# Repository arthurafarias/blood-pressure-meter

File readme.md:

# IoT Measurement Endpoint

A KiCad PCB design for a wireless IoT node that reads analog sensors and drives actuators (DC motor and solenoid valve). Built around the ESP32-C3 module for WiFi/BLE connectivity.

## Features

- **ESP32-C3-WROOM-02** — WiFi 4 + Bluetooth LE microcontroller module
- **Analog sensor front-end** — LM324 quad op-amp for signal conditioning
- **Actuator outputs** — DMC2053UVT complementary MOSFET pair for a DC motor and a solenoid valve
- **USB-C** — CH330N USB-to-UART bridge for programming and serial debug; TVS + common-mode choke for ESD/EMI protection
- **Power** — battery connector with 5V USB-C input; NCP1117-3.3 LDO generates the 3.3V rail; polyfuse (0402L050SL) for overcurrent protection
- **User interface** — tactile push buttons (KMR232NG) and status LEDs
- **Fabrication aids** — fiducials, mounting holes, and test points throughout

## Schematic sheets

| Sheet | Contents |
|---|---|
| Top-level | Sheet hierarchy and inter-sheet connections |
| Microcontroller | ESP32-C3-WROOM-02 and decoupling |
| Sensor | LM324 op-amp conditioning circuit |
| Motor | DC motor MOSFET driver with flyback diode |
| Valve | Solenoid valve MOSFET driver |
| 3.3V Regulator | NCP1117-3.3 LDO and bulk capacitors |
| USB Connector | USB-C, CH330N, common-mode choke, TVS array |
| Battery Connector | Battery input and protection diodes |
| Buttons | Tactile switch debounce network |
| LEDs | Status indicators |

## Power architecture

```
USB-C (5V) ──┬── CH330N (serial) ──► UART ──► ESP32-C3
             │
Battery ─────┴── NCP1117-3.3 ──► 3.3V rail ──► ESP32-C3, LM324, logic
                                               └── actuator gate drives

Actuators driven from +6V / +5V rail (motor, valve)
```

## Key components

| Reference | Part | Description |
|---|---|---|
| U (MCU) | ESP32-C3-WROOM-02 | WiFi 4 / BLE 5 module |
| U (USB) | CH330N | USB-to-UART converter, SOIC-8 |
| U (reg) | NCP1117-3.3 | 1A LDO, SOT-223 |
| U (amp) | LM324 | Quad op-amp, DIP-14/SOIC-14 |
| Q | DMC2053UVT | Complementary P+N MOSFET pair, TSOT-23-6 |
| D (ESD) | ESD9B5.0ST5G | TVS diode, signal lines |
| D (USB TVS) | WE-TVS-82400102 | Low-cap TVS array, SOT-23-6 |
| L (USB filter) | 0603USB-142 | Common-mode choke, 98nH, 500mA |
| F | 0402L050SL | Resettable polyfuse |
| SW | KMR232NG ULC LFS | Tactile push button |

## Tools

- **EDA**: KiCad 10.0
- **Simulation**: ngspice (`.cir` files in repo for op-amp circuit verification)
- **3D export**: STEP / STL / GLB (see `iot-measurement-endpoint.step`)

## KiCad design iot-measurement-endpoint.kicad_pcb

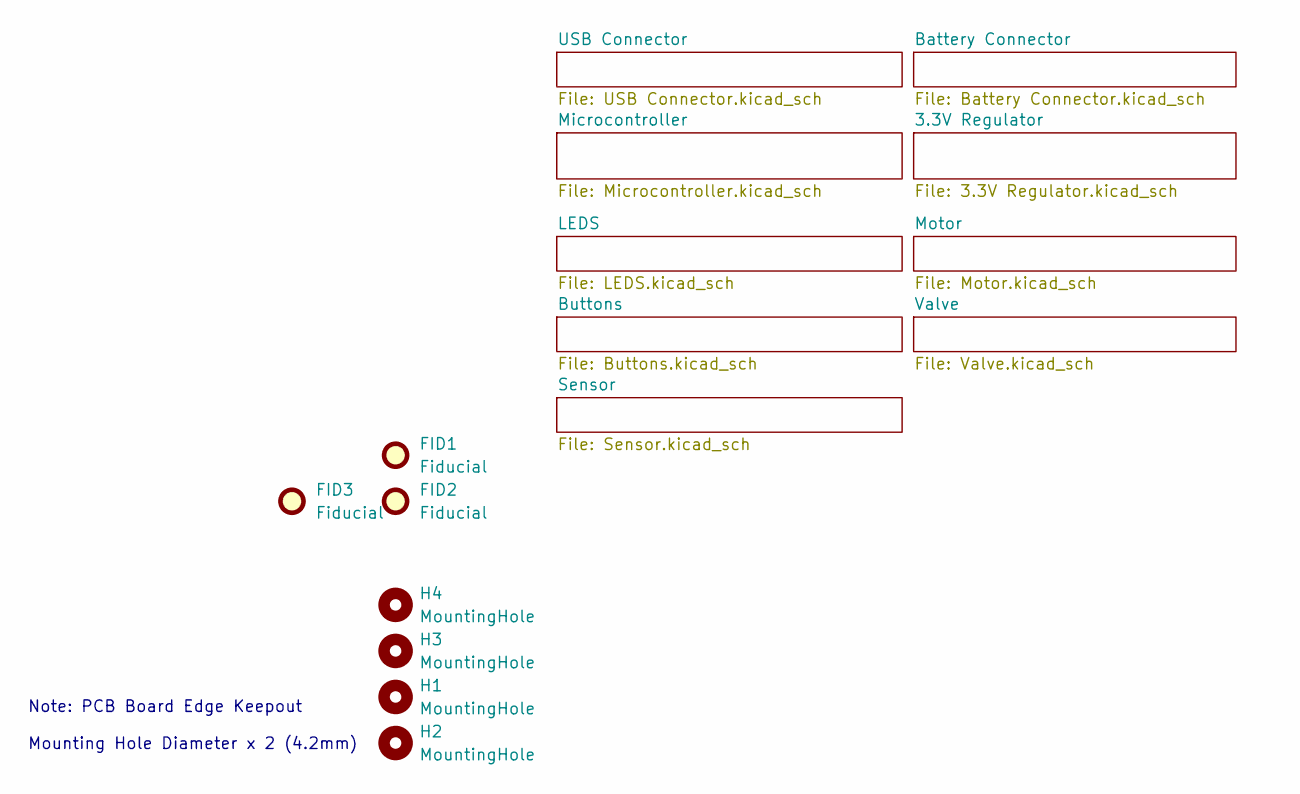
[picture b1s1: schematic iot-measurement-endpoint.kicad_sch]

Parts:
FID1: Fiducial; Fiducial_Cross_1.5mm_Mask2mm
FID2, FID3: Fiducial; Fiducial_0.5mm_Mask1.5mm
H1, H2, H3, H4: MountingHole; MountingHole_2.1mm

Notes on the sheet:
Note: PCB Board Edge Keepout Mounting Hole Diameter x 2 (4.2mm)

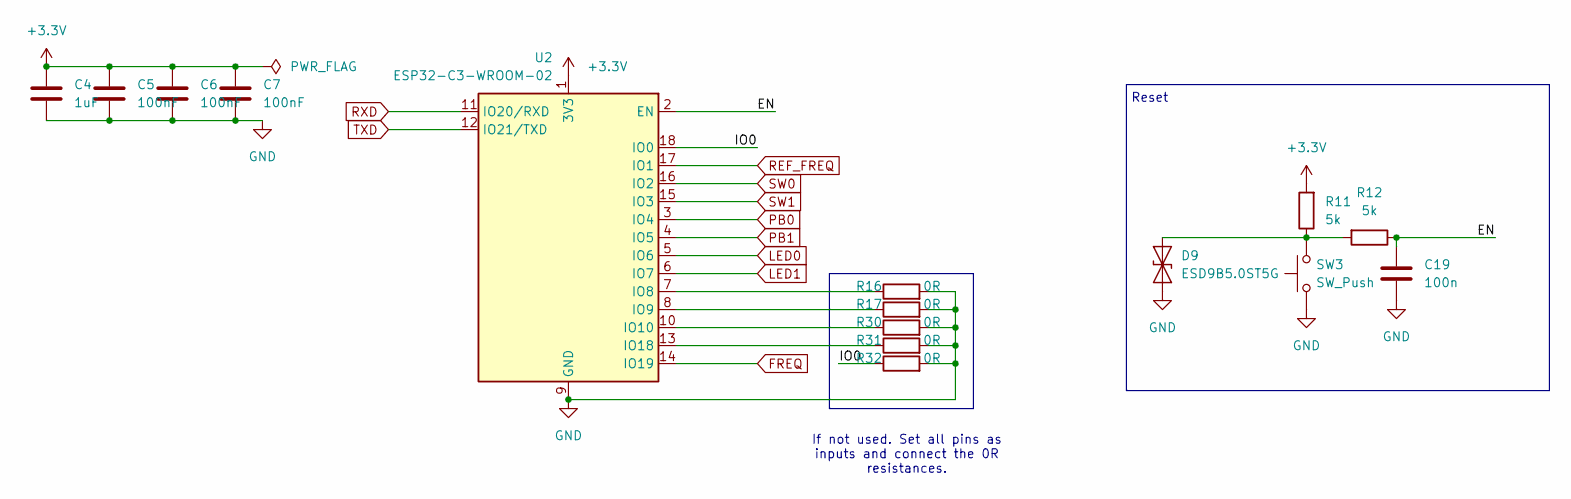
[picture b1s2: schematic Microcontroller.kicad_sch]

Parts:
C4: 1uF; C_0402_1005Metric
C5, C6, C7: 100nF; C_0402_1005Metric
C19: 100n; C_0402_1005Metric
D9: ESD9B5.0ST5G; D_SOD-923
R11, R12: 5k; R_0402_1005Metric
R16, R17, R30, R31, R32: 0R; R_0402_1005Metric
SW3: SW_Push; SW_Push_1P1T_NO_CK_KMR2
U2: ESP32-C3-WROOM-02

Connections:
+3.3V: C4.1, C5.1, C6.1, C7.1, R11.2, U2.1 (3V3); also elsewhere on the board
/Microcontroller/EN: C19.1, R12.1, U2.2 (EN)
/Microcontroller/IO0: R32.1, U2.18 (IO0)
FREQ: U2.14 (IO19); also elsewhere on the board
GND: C4.2, C5.2, C6.2, C7.2, C19.2, D9.1 (A1), R16.2, R17.2, R30.2, R31.2, R32.2, SW3.1, U2.9 (GND), U2.19 (GND); also elsewhere on the board
LED0: U2.5 (IO6); also elsewhere on the board
LED1: U2.6 (IO7); also elsewhere on the board
unnamed: D9.2 (A2), R11.1, R12.2, SW3.2
unnamed: R16.1, U2.7 (IO8)
unnamed: R17.1, U2.8 (IO9)
unnamed: R30.1, U2.10 (IO10)
unnamed: R31.1, U2.13 (IO18)
PB0: U2.3 (IO4); also elsewhere on the board
PB1: U2.4 (IO5); also elsewhere on the board
REF_FREQ: U2.17 (IO1); also elsewhere on the board
RXD: U2.11 (IO20/RXD); also elsewhere on the board
SW0: U2.16 (IO2); also elsewhere on the board
SW1: U2.15 (IO3); also elsewhere on the board
TXD: U2.12 (IO21/TXD); also elsewhere on the board

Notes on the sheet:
Reset
If not used. Set all pins as inputs and connect the 0R resistances.

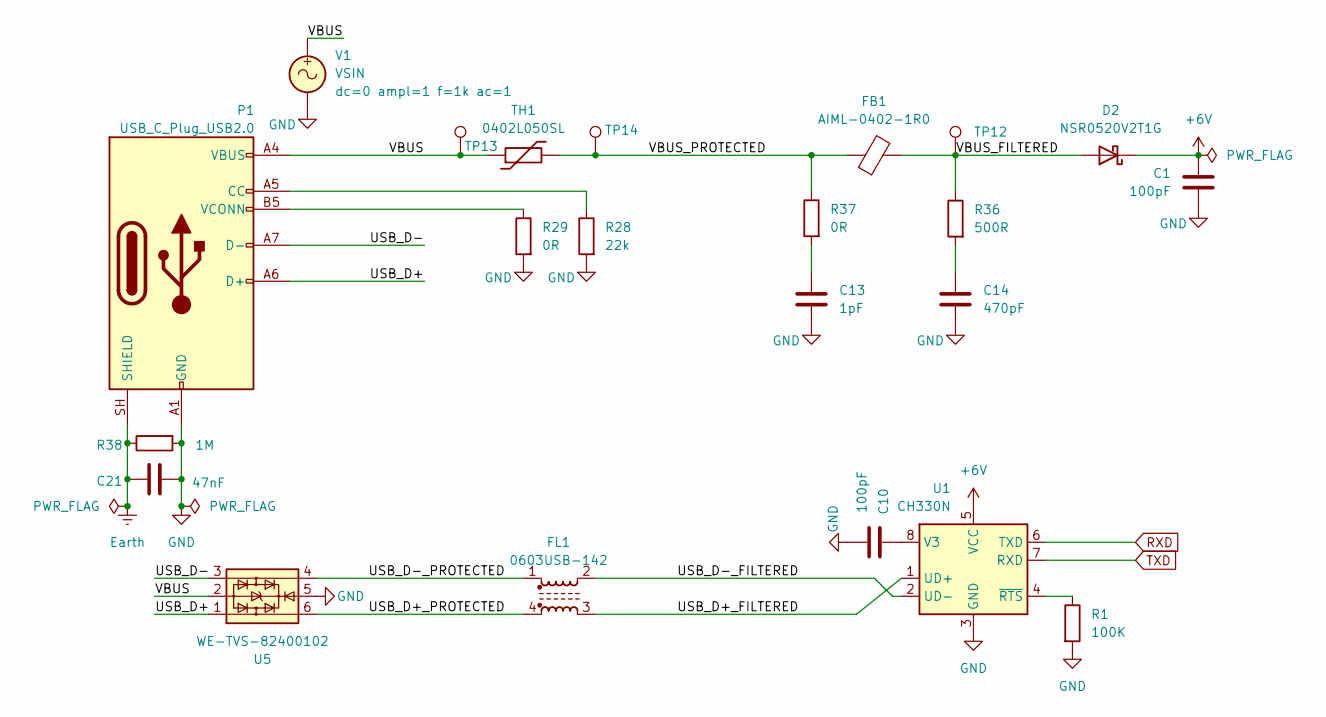
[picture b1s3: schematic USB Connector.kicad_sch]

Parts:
C1, C10: 100pF; C_0402_1005Metric
C13: 1pF; C_0402_1005Metric
C14: 470pF; C_0402_1005Metric
C21: 47nF; C_0402_1005Metric
D2: NSR0520V2T1G; D_0402_1005Metric
FB1: AIML-0402-1R0; L_0402_1005Metric
FL1: 0603USB-142; L_CommonModeChoke_Coilcraft_0603USB
P1: USB_C_Plug_USB2.0; USB_C_Receptacle_Amphenol_12401548E4-2A_CircularHoles
R1: 100K; R_0402_1005Metric
R28: 22k; R_0402_1005Metric
R29, R37: 0R; R_0402_1005Metric
R36: 500R; R_0402_1005Metric
R38: 1M; R_0402_1005Metric
TH1: 0402L050SL; R_0402_1005Metric
TP12, TP13, TP14: TestPoint; TestPoint_Pad_D1.0mm
U1: CH330N; SOIC-8_3.9x4.9mm_P1.27mm
U5: WE-TVS-82400102; SOT-23-6
V1: VSIN

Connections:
+6V: C1.1, D2.1 (K), U1.5 (VCC); also elsewhere on the board
/USB Connector/USB_D+: P1.A6 (D+), U5.1
/USB Connector/USB_D+_FILTERED: FL1.3, U1.1 (UD+)
/USB Connector/USB_D+_PROTECTED: FL1.4, U5.6
/USB Connector/USB_D-: P1.A7 (D-), U5.3
/USB Connector/USB_D-_FILTERED: FL1.2, U1.2 (UD-)
/USB Connector/USB_D-_PROTECTED: FL1.1, U5.4
/USB Connector/VBUS: P1.A4 (VBUS), P1.A9 (VBUS), P1.B4 (VBUS), P1.B9 (VBUS), TH1.1, TP13.1 (1_1), U5.2, V1.1
/USB Connector/VBUS_FILTERED: D2.2 (A), FB1.2, R36.1, TP12.1 (1_1)
/USB Connector/VBUS_PROTECTED: FB1.1, R37.1, TH1.2, TP14.1 (1_1)
Earth: C21.1, P1.SH (SHIELD), R38.1
GND: C1.2, C10.2, C13.2, C14.2, C21.2, P1.A1 (GND), P1.A12 (GND), P1.B1 (GND), P1.B12 (GND), R1.2, R28.2, R29.2, R38.2, U1.3 (GND), U5.5, V1.2; also elsewhere on the board
unnamed: C13.1, R37.2
unnamed: C14.1, R36.2
unnamed: P1.A5 (CC), R28.1
unnamed: P1.B5 (VCONN), R29.1
unnamed: C10.1, U1.8 (V3)
unnamed: R1.1, U1.4 (~RTS)
RXD: U1.6 (TXD); also elsewhere on the board
TXD: U1.7 (RXD); also elsewhere on the board

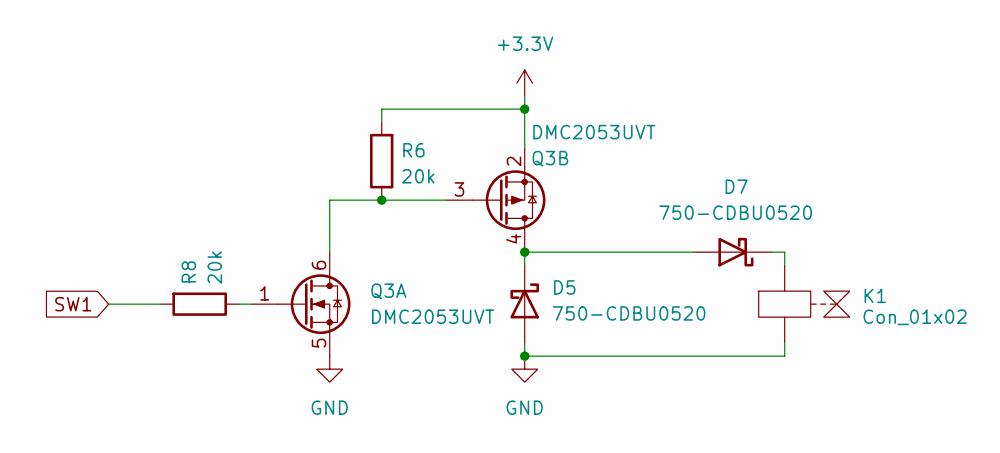
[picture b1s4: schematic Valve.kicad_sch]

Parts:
D5, D7: 750-CDBU0520; D_0603_1608Metric
K1: Con_01x02; Hirose_DF13-02P-1.25DSA_1x02_P1.25mm_Vertical
Q3: DMC2053UVT; TSOT-23-6
R6, R8: 20k; R_0402_1005Metric

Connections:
+3.3V: Q3.2 (S), R6.2; also elsewhere on the board
GND: D5.2 (A), K1.2 (A), Q3.5 (S); also elsewhere on the board
unnamed: D5.1 (K), D7.2 (A), Q3.4 (D)
unnamed: D7.1 (K), K1.1 (K)
unnamed: Q3.3 (G), Q3.6 (D), R6.1
unnamed: Q3.1 (G), R8.1
SW1: R8.2; also elsewhere on the board

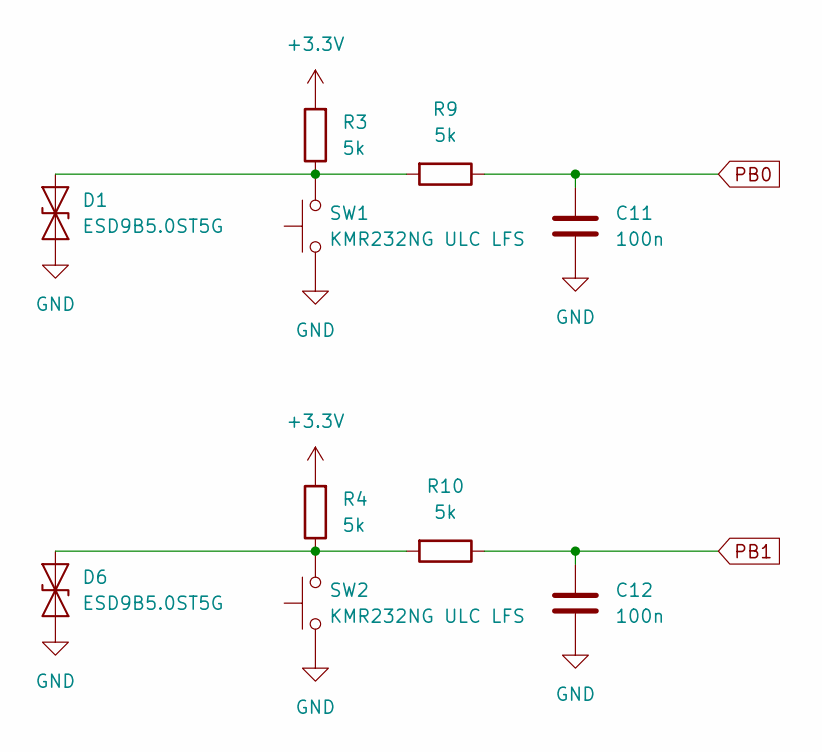
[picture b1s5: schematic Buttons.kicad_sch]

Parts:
C11, C12: 100n; C_0402_1005Metric
D1, D6: ESD9B5.0ST5G; D_SOD-923
R3, R4, R9, R10: 5k; R_0402_1005Metric
SW1, SW2: KMR232NG ULC LFS; SW_Push_1P1T_NO_CK_KMR2

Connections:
+3.3V: R3.2, R4.2; also elsewhere on the board
GND: C11.2, C12.2, D1.1 (A1), D6.1 (A1), SW1.1, SW2.1; also elsewhere on the board
unnamed: D1.2 (A2), R3.1, R9.2, SW1.2
unnamed: D6.2 (A2), R4.1, R10.2, SW2.2
PB0: C11.1, R9.1; also elsewhere on the board
PB1: C12.1, R10.1; also elsewhere on the board

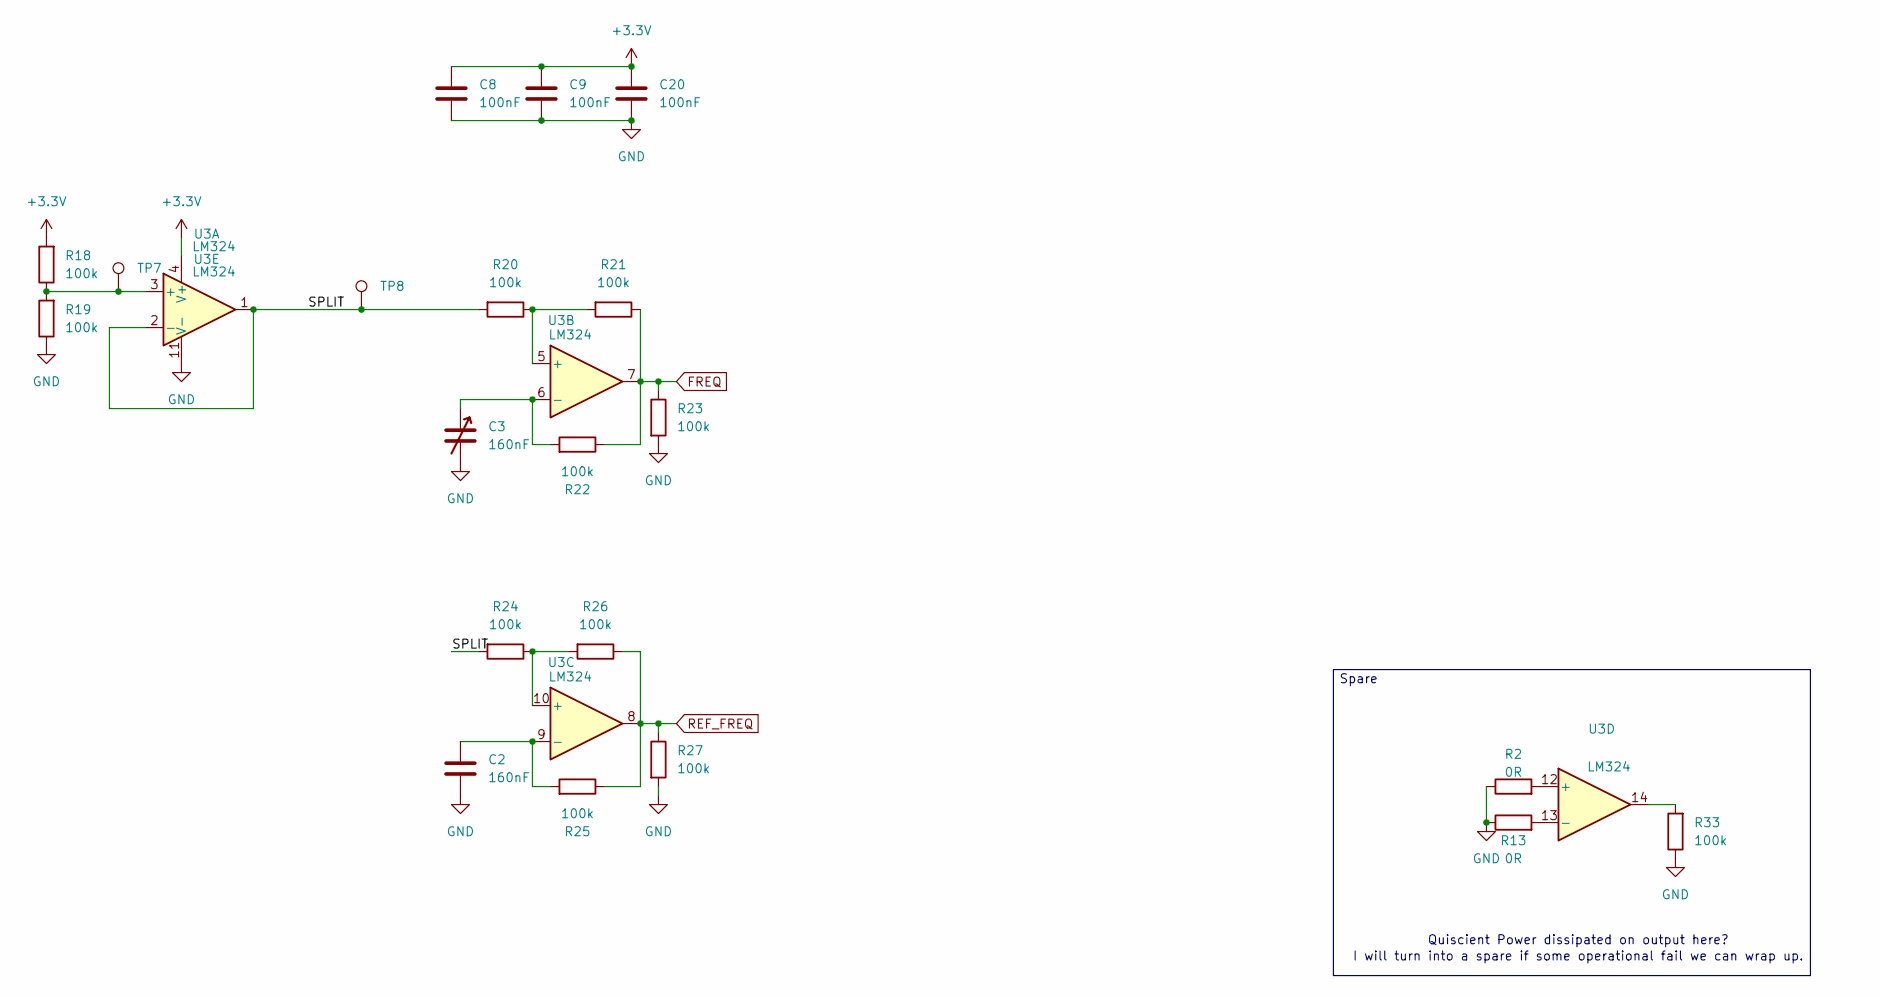
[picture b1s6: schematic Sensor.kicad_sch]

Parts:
C2: 160nF; C_0402_1005Metric
C3: 160nF; Hirose_DF13-02P-1.25DSA_1x02_P1.25mm_Vertical
C8, C9, C20: 100nF; C_0402_1005Metric
R2, R13: 0R; R_0402_1005Metric
R18, R19, R20, R21, R22, R23, R24, R25, R26, R27, R33: 100k; R_0402_1005Metric
TP7, TP8: TestPoint; TestPoint_Pad_D1.0mm
U3: LM324; WQFN-16-1EP_3x3mm_P0.5mm_EP1.68x1.68mm

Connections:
+3.3V: C8.1, C9.1, C20.1, R18.2, U3.4 (V+); also elsewhere on the board
/Sensor/SPLIT: R20.2, R24.2, TP8.1 (1_1), U3.1, U3.2 (-)
FREQ: R21.1, R22.1, R23.1, U3.7; also elsewhere on the board
GND: C2.2, C3.2, C8.2, C9.2, C20.2, R2.1, R13.1, R19.1, R23.2, R27.2, R33.1, U3.11 (V-); also elsewhere on the board
unnamed: R33.2, U3.14
unnamed: R18.1, R19.2, TP7.1 (1_1), U3.3 (+)
unnamed: R20.1, R21.2, U3.5 (+)
unnamed: C3.1, R22.2, U3.6 (-)
unnamed: R24.1, R26.2, U3.10 (+)
unnamed: C2.1, R25.2, U3.9 (-)
unnamed: R2.2, U3.12 (+)
unnamed: R13.2, U3.13 (-)
REF_FREQ: R25.1, R26.1, R27.1, U3.8; also elsewhere on the board

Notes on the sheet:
Quiscient Power dissipated on output here?
I will turn into a spare if some operational fail we can wrap up.
Spare

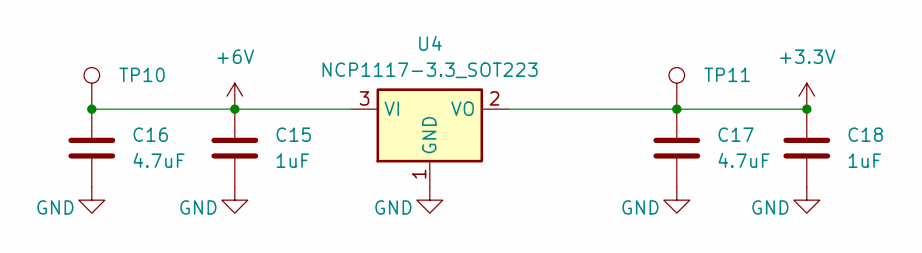
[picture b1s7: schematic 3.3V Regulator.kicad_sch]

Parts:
C15, C18: 1uF; C_0402_1005Metric
C16, C17: 4.7uF; C_0603_1608Metric
TP10, TP11: TestPoint; TestPoint_Pad_D1.0mm
U4: NCP1117-3.3_SOT223; SOT-223-3_TabPin2

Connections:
+3.3V: C17.1, C18.1, TP11.1 (1_1), U4.2 (VO); also elsewhere on the board
+6V: C15.1, C16.1, TP10.1 (1_1), U4.3 (VI); also elsewhere on the board
GND: C15.2, C16.2, C17.2, C18.2, U4.1 (GND); also elsewhere on the board

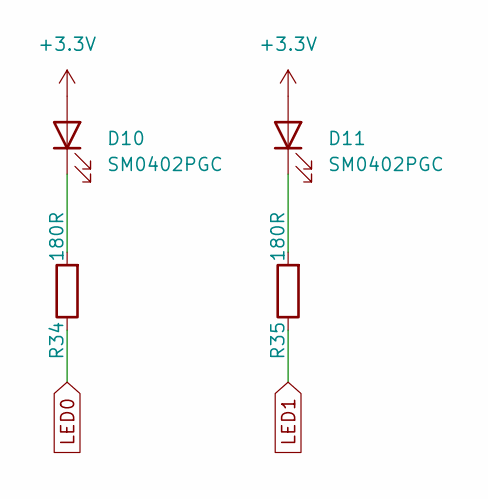
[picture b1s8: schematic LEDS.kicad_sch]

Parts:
D10, D11: SM0402PGC; D_0402_1005Metric
R34, R35: 180R; R_0402_1005Metric

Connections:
+3.3V: D10.2 (A), D11.2 (A); also elsewhere on the board
LED0: R34.1; also elsewhere on the board
LED1: R35.1; also elsewhere on the board
unnamed: D10.1 (K), R34.2
unnamed: D11.1 (K), R35.2

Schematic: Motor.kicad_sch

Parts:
D4, D8: 750-CDBU0520; D_0603_1608Metric
M1: Motor_DC; Hirose_DF13-02P-1.25DSA_1x02_P1.25mm_Vertical
Q2: DMC2053UVT; TSOT-23-6
R5, R7: 20k; R_0402_1005Metric

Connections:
+6V: Q2.2 (S), R5.2; also elsewhere on the board
GND: D4.2 (A), M1.2 (-), Q2.5 (S); also elsewhere on the board
unnamed: D4.1 (K), D8.2 (A), Q2.4 (D)
unnamed: D8.1 (K), M1.1 (+)
unnamed: Q2.3 (G), Q2.6 (D), R5.1
unnamed: Q2.1 (G), R7.1
SW0: R7.2; also elsewhere on the board

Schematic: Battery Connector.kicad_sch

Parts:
BT1: Battery; Hirose_DF13-02P-1.25DSA_1x02_P1.25mm_Vertical
D3: 750-CDBU0520; D_0603_1608Metric
TP9: TestPoint; TestPoint_Pad_D1.0mm

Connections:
+6V: D3.1 (K); also elsewhere on the board
GND: BT1.2 (-); also elsewhere on the board
unnamed: BT1.1 (+), D3.2 (A), TP9.1 (1_1)

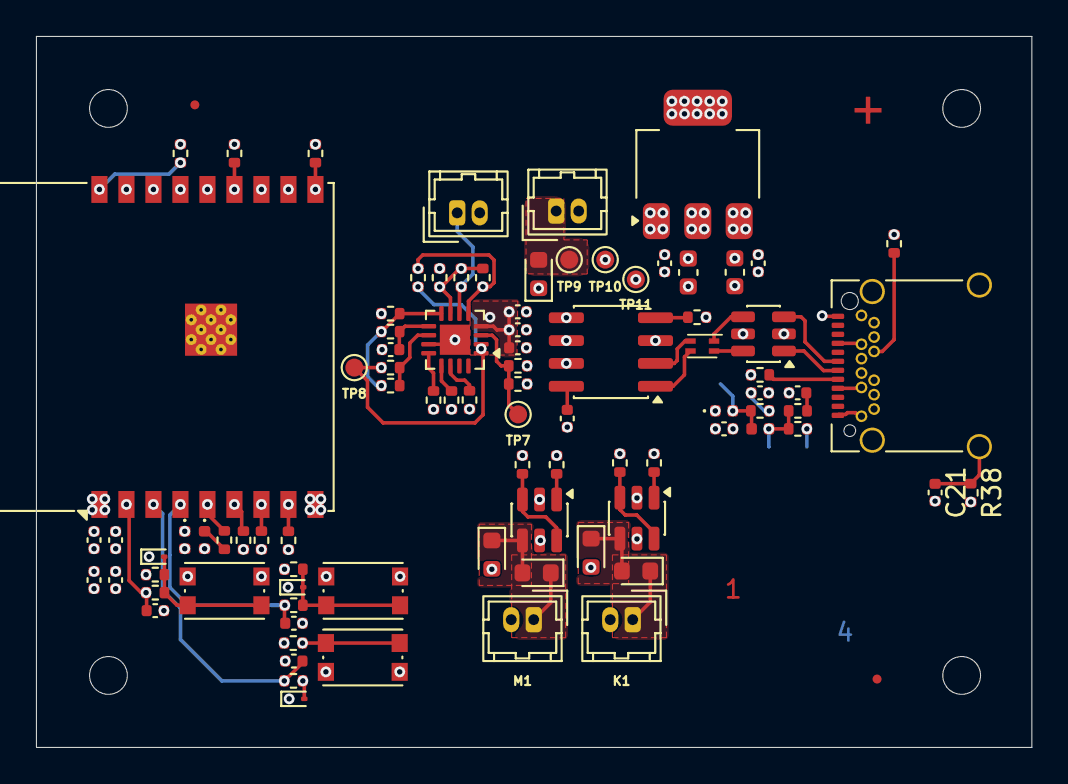
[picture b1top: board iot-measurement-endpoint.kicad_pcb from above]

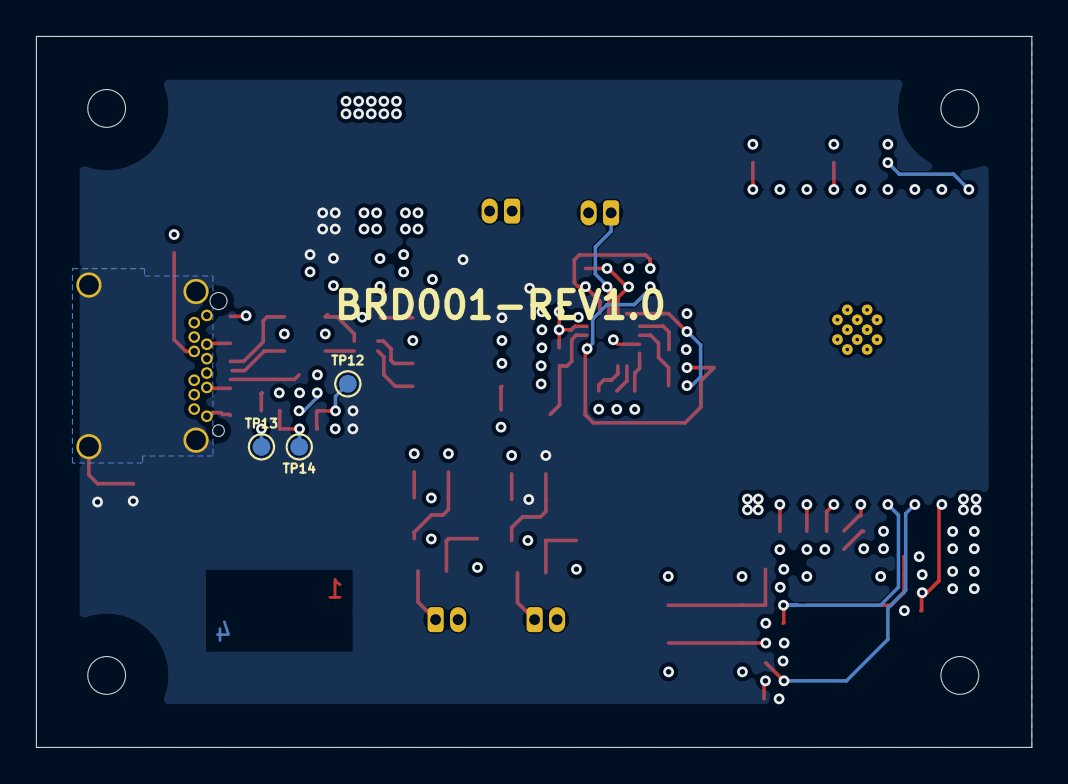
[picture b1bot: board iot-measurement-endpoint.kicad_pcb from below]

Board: 4 copper layers, 55.3 x 39.5 mm, 100 parts (3 on the bottom side), 58 nets.

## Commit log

2026-06-22 Fixing power planes for motor and valve outputs
2026-06-22 Fixing filter response to put loads at 10 MHz signals and 1 GHz signals (low pass RC and ferrite) at DC power supply (rejecting high frequency noise in the power supply).
2026-06-22 Routing improvement
2026-06-22 Changing placement image from readme.md
2026-06-22 Unifying 3.3V plane with the regulator output (removing net tie)
2026-06-22 Reducing VBUS area to remove 3.3V plane discontinuity
2026-06-22 Adding resistance and capacitance connecting GND and Earth in the peripheral device
